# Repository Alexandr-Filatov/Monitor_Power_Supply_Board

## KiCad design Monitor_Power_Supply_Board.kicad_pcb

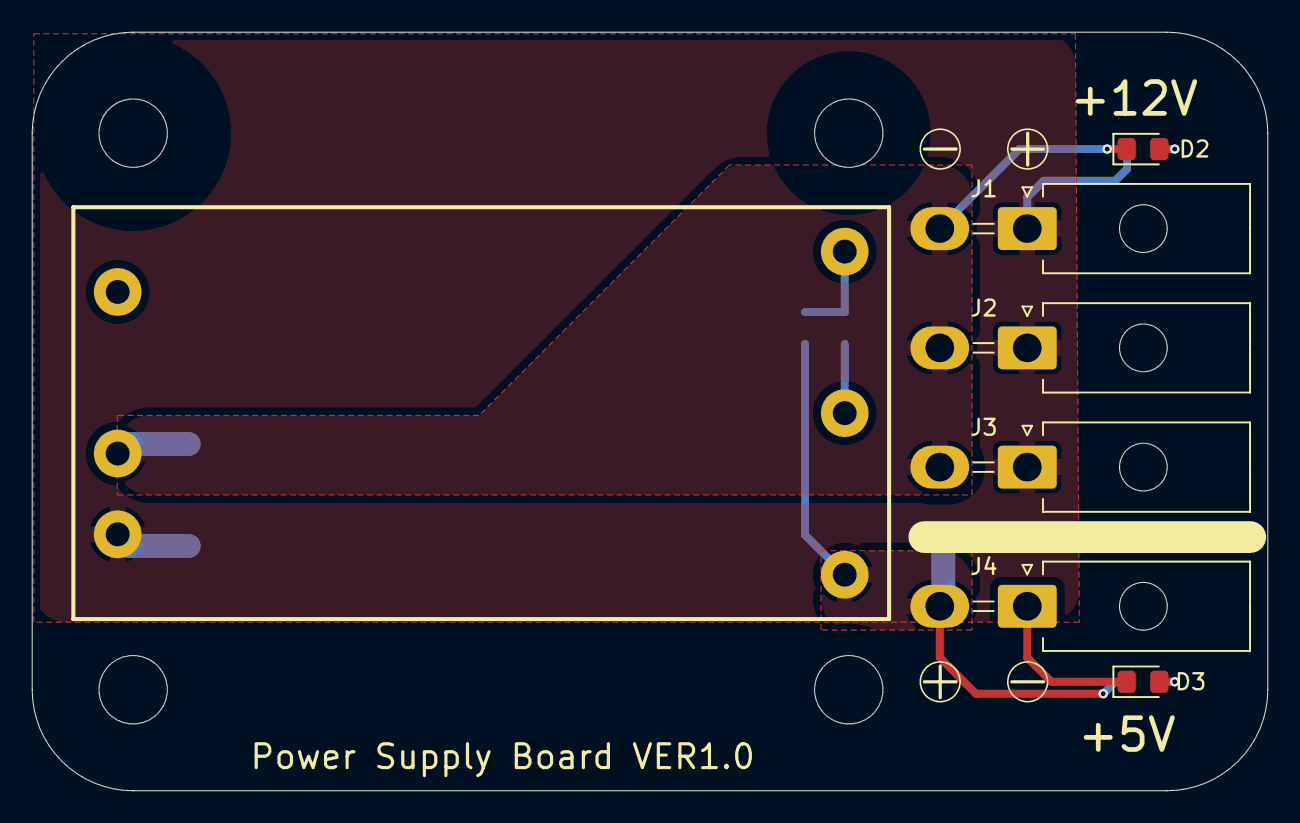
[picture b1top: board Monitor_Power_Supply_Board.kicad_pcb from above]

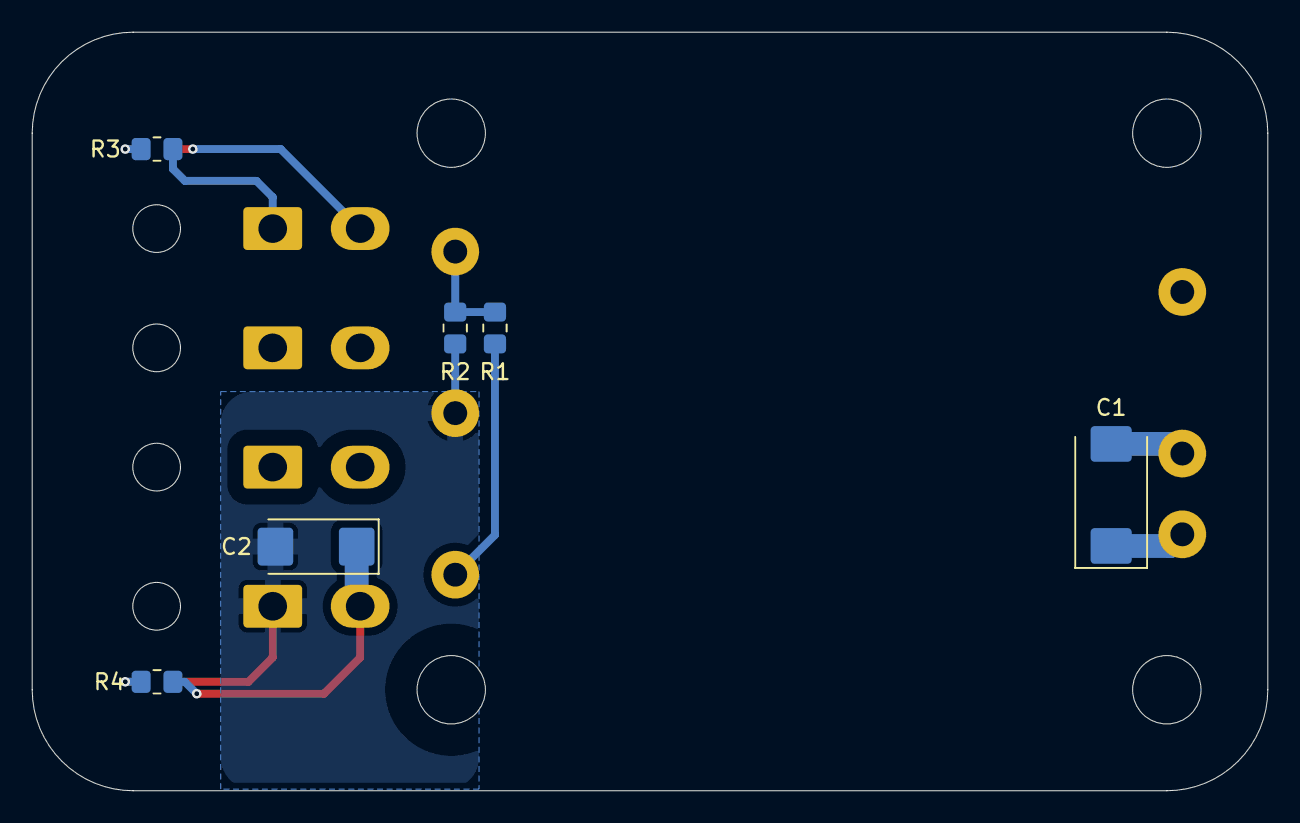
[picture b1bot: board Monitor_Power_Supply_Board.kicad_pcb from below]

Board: 2 copper layers, 77.7 x 47.7 mm, 17 parts (6 on the bottom side), 7 nets.

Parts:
C1: 47u; CP_EIA-7343-31_Kemet-D_HandSolder
C2: 220u; CP_EIA-6032-28_Kemet-C_HandSolder
D1: SKM30F-05N
D2, D3: LED_Small; LED_0805_2012Metric_Pad1.15x1.40mm_HandSolder
H1, H2, H3, H4: MountingHole; MountingHole_4.3mm_M4
J1, J2, J3, J4: Conn_01x02; Molex_Mini-Fit_Jr_5569-02A2_2x01_P4.20mm_Horizontal
R1, R2: R_0805_2012Metric_Pad1.20x1.40mm_HandSolder
R3: 2k; R_0805_2012Metric_Pad1.20x1.40mm_HandSolder
R4: 1k; R_0805_2012Metric_Pad1.20x1.40mm_HandSolder

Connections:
+5V: C2.1, D1.4 (+Vout), J4.2, R1.1, R4.1
GND: C2.2, D1.5 (-Vout), D3.1 (K), J4.1, R2.2
unnamed: D1.6 (Trim), R1.2, R2.1
unnamed: D2.2 (A), R3.2
unnamed: D3.2 (A), R4.2
VDD: C1.1, D1.1 (+Vin), J1.1, J2.1, J3.1, R3.1
VSS: C1.2, D1.2 (-Vin), D2.1 (K), J1.2, J2.2, J3.2

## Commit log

2025-09-04 VER1.0: zero commit
2025-09-05 test commit
2025-09-16 VER1.0: добавил разъем для вентилятора и индикацию питания
2025-09-16 VER1.0: добавил шелкографию полярности питания
2025-09-19 VER1.0: отправил в резонит
2025-11-19 VER1.0: добавил кд в папку Docs
2025-11-20 VER1.0: исправил сборочный чертеж
2025-12-01 VER1.0: исправил Э3
2025-12-01 VER1.0: исправил CБ
